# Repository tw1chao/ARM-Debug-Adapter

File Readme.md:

# Why create this repository

I bought Segger J-Link EDU Mini [^SeggerJlinkMini] and STLink V3 mini[^STLINK-V3MODS] (STDC14 Connect) but the connector pitch is 1.27mm, so I couldn't use it to debug the current board, then I designed a debug circuit adapter and opened the source.I made this circuit from Pickit4 debug adapter board [^PICKit-DABTP] product idea.

I used kicad[^KICAD] to design the circuit diagram and layout of the printed circuit board.

- [For STLink V3 mini adapter board repository](https://github.com/tw1chao/STLinkV3_Adapter)

# Schematic

# PCB

[^STLINK-V3MODS]:[UM2502 STLINK-V3MODS and STLINK-V3MINI debugger/programmer tiny probes for STM32 microcontrollers](https://www.st.com/resource/en/user_manual/um2502-stlinkv3mods-and-stlinkv3mini-debuggerprogrammer-tiny-probes-for-stm32-microcontrollers-stmicroelectronics.pdf)

[^PICKit-DABTP]:[PICkit™4 Debugger Adapter Board Target Pinouts](https://microchipdeveloper.com/pickit4:debugger-adapter-pinouts)

[^SeggerJlinkMini]:[The small-size educational debug probe](https://www.segger.com/products/debug-probes/j-link/models/j-link-edu-mini/)

[^KICAD]:[A Cross Platform and Open Source Electronics Design Automation Suite](https://www.kicad.org/)

# License

- Hardware in this repository is licensed under CERN OHL v2.0
[**CERN-OHL-S**](https://ohwr.org/cern_ohl_s_v2.pdf)

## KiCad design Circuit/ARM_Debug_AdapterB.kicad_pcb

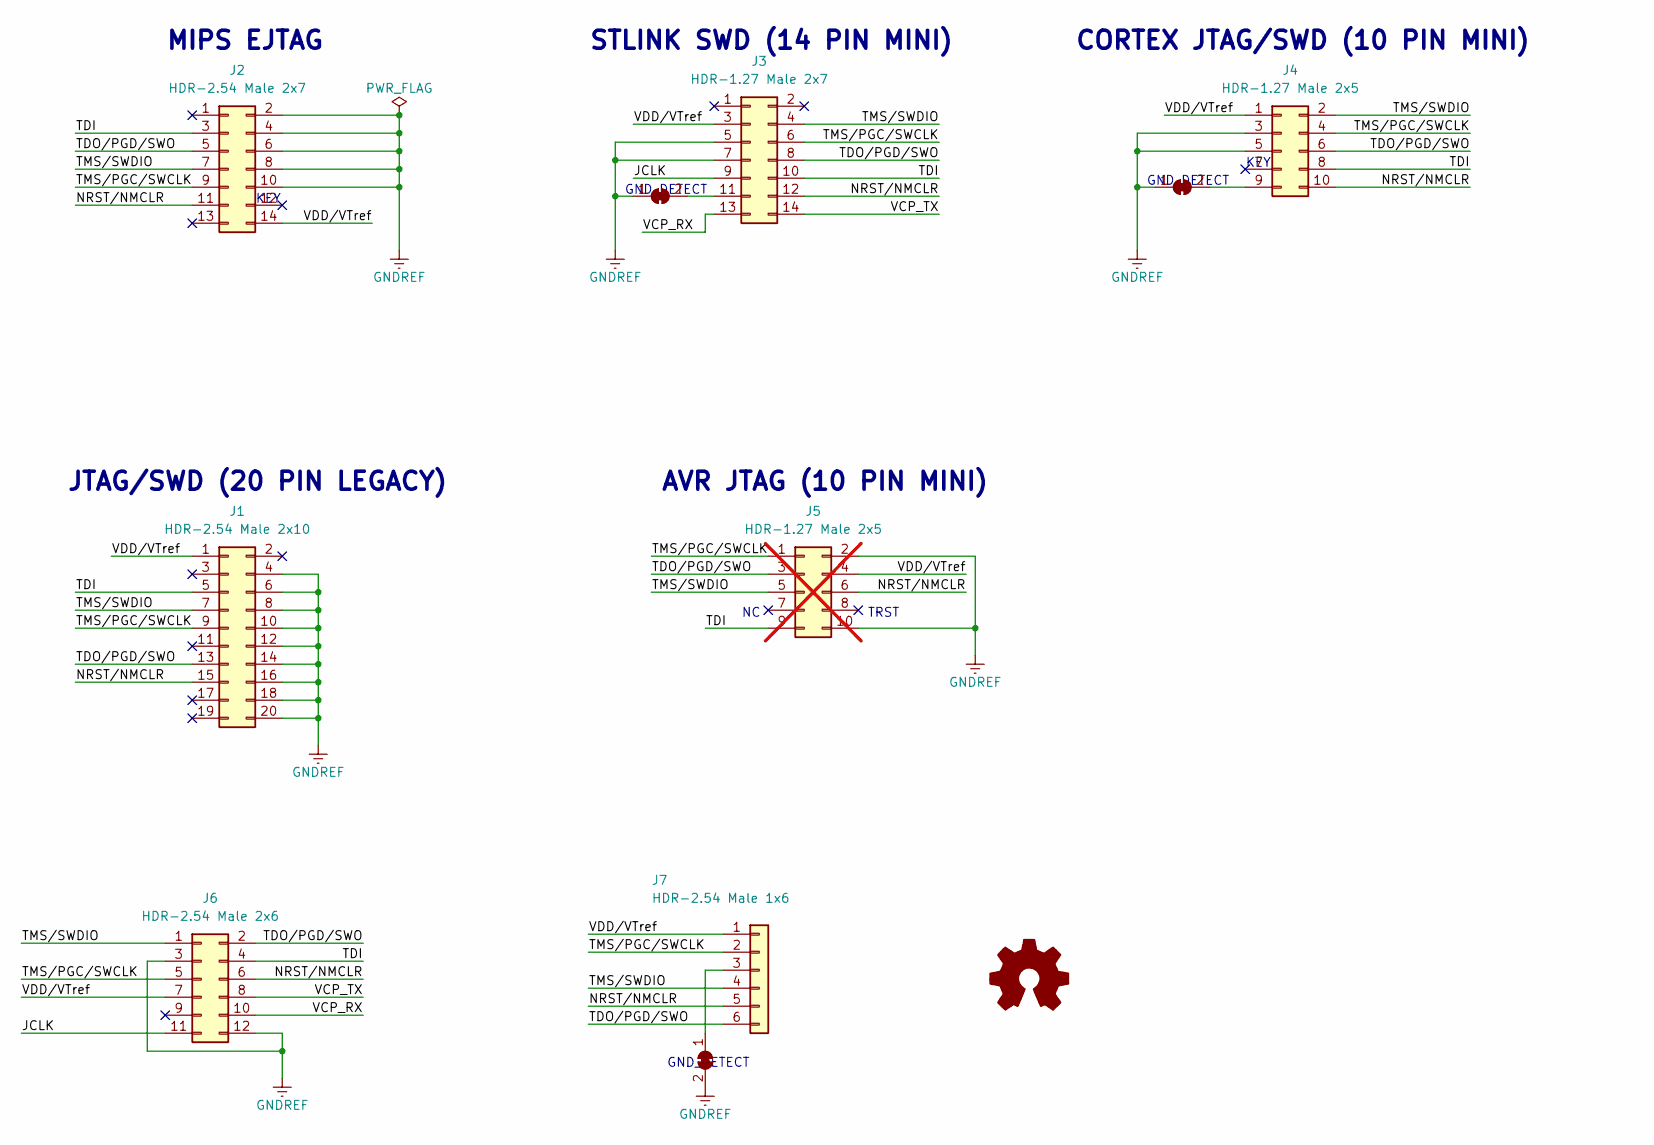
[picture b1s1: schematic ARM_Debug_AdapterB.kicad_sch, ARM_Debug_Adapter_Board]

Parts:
J1: HDR-2.54 Male 2x10; IDC-Header_2x10_P2.54mm_Vertical
J2: HDR-2.54 Male 2x7; IDC-Header_2x07_P2.54mm_Vertical
J3: HDR-1.27 Male 2x7; PinHeader_2x07_P1.27mm_Vertical_SMD
J4: HDR-1.27 Male 2x5; PinHeader_2x05_P1.27mm_Vertical
J5: HDR-1.27 Male 2x5; PinHeader_2x05_P1.27mm_Vertical; not fitted
J6: HDR-2.54 Male 2x6; PinHeader_2x06_P2.54mm_Vertical
J7: HDR-2.54 Male 1x6; PinHeader_1x06_P2.54mm_Vertical
JP1, JP2, JP3: SolderJumper_2_Bridged; SolderJumper-2_P1.3mm_Bridged_RoundedPad1.0x1.5mm

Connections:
/JCLK: J3.9, J6.11
/NRST/NMCLR: J1.15, J2.11, J3.12, J4.10, J5.6, J6.6, J7.5
/TDI: J1.5, J2.3, J3.10, J4.8, J5.9, J6.4
/TDO/PGD/SWO: J1.13, J2.5, J3.8, J4.6, J5.3, J6.2, J7.6
/TMS/PGC/SWCLK: J1.9, J2.9, J3.6, J4.4, J5.1, J6.5, J7.2
/TMS/SWDIO: J1.7, J2.7, J3.4, J4.2, J5.5, J6.1, J7.4
/VCP_RX: J3.13, J6.10
/VCP_TX: J3.14, J6.8
/VDD/VTref: J1.1, J2.14, J3.3, J4.1, J5.4, J6.7, J7.1
GNDREF: J1.4, J1.6, J1.8, J1.10, J1.12, J1.14, J1.16, J1.18, J1.20, J2.2, J2.4, J2.6, J2.8, J2.10, J3.5, J3.7, J4.3, J4.5, J5.2, J5.10, J6.3, J6.12, JP1.1 (A), JP2.1 (A), JP3.2 (B)
unnamed: J3.11, JP1.2 (B)
unnamed: J4.9, JP2.2 (B)
unnamed: J7.3, JP3.1 (A)

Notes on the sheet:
GND_DETECT
KEY
JTAG/SWD (20 PIN LEGACY)
CORTEX JTAG/SWD (10 PIN MINI)
MIPS EJTAG
AVR JTAG (10 PIN MINI)
TRST
STLINK SWD (14 PIN MINI)

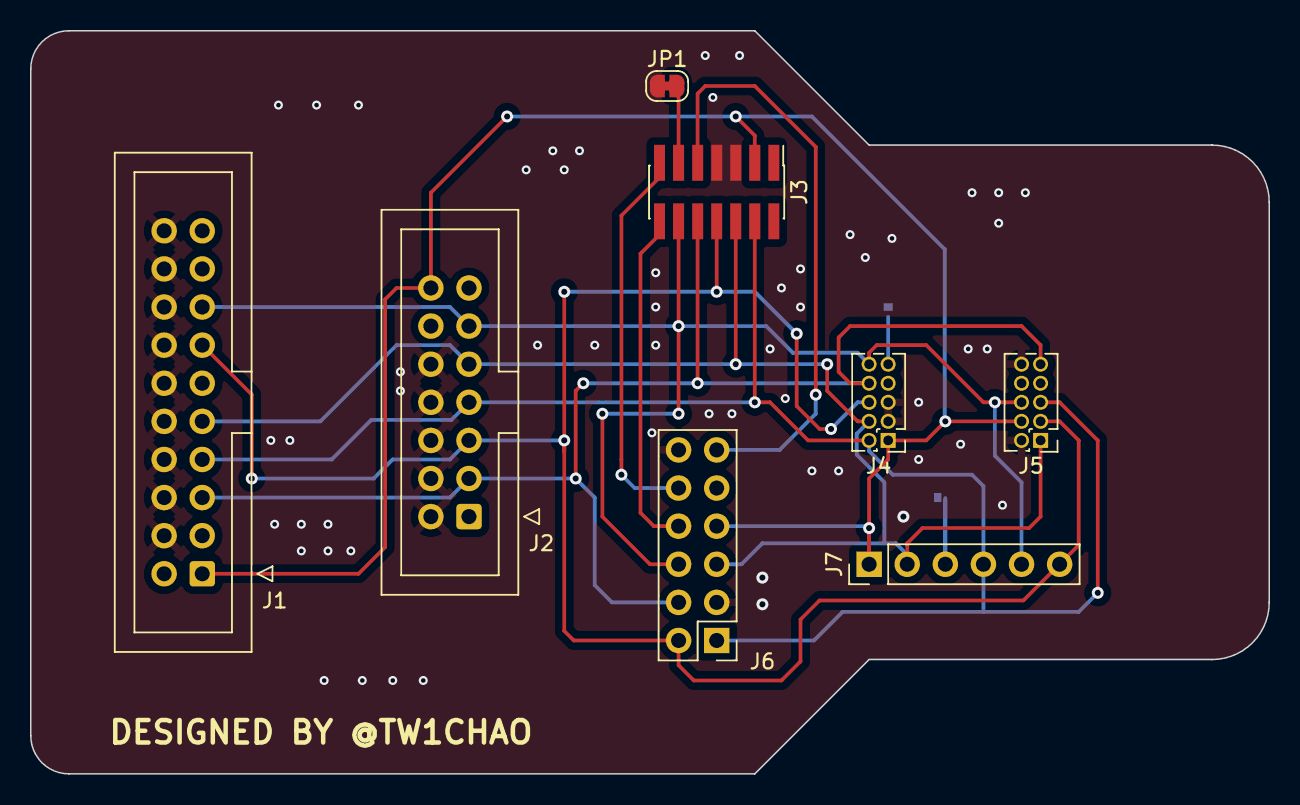
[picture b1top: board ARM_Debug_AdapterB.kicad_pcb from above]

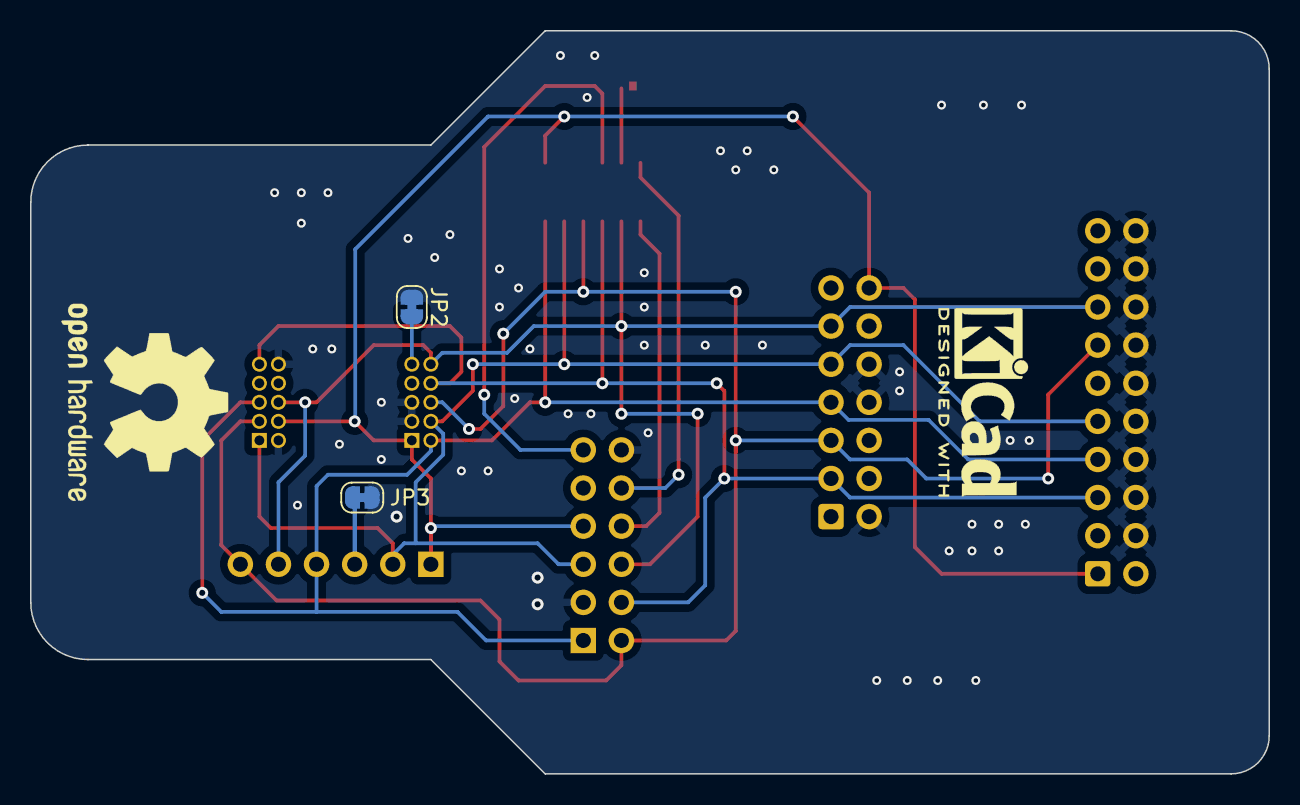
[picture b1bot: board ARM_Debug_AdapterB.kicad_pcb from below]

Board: 2 copper layers, 82.5 x 49.5 mm, 10 parts (2 on the bottom side), 13 nets.

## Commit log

2023-06-03 update PCB Trace Routing
2023-06-12 Completed PCB routing
